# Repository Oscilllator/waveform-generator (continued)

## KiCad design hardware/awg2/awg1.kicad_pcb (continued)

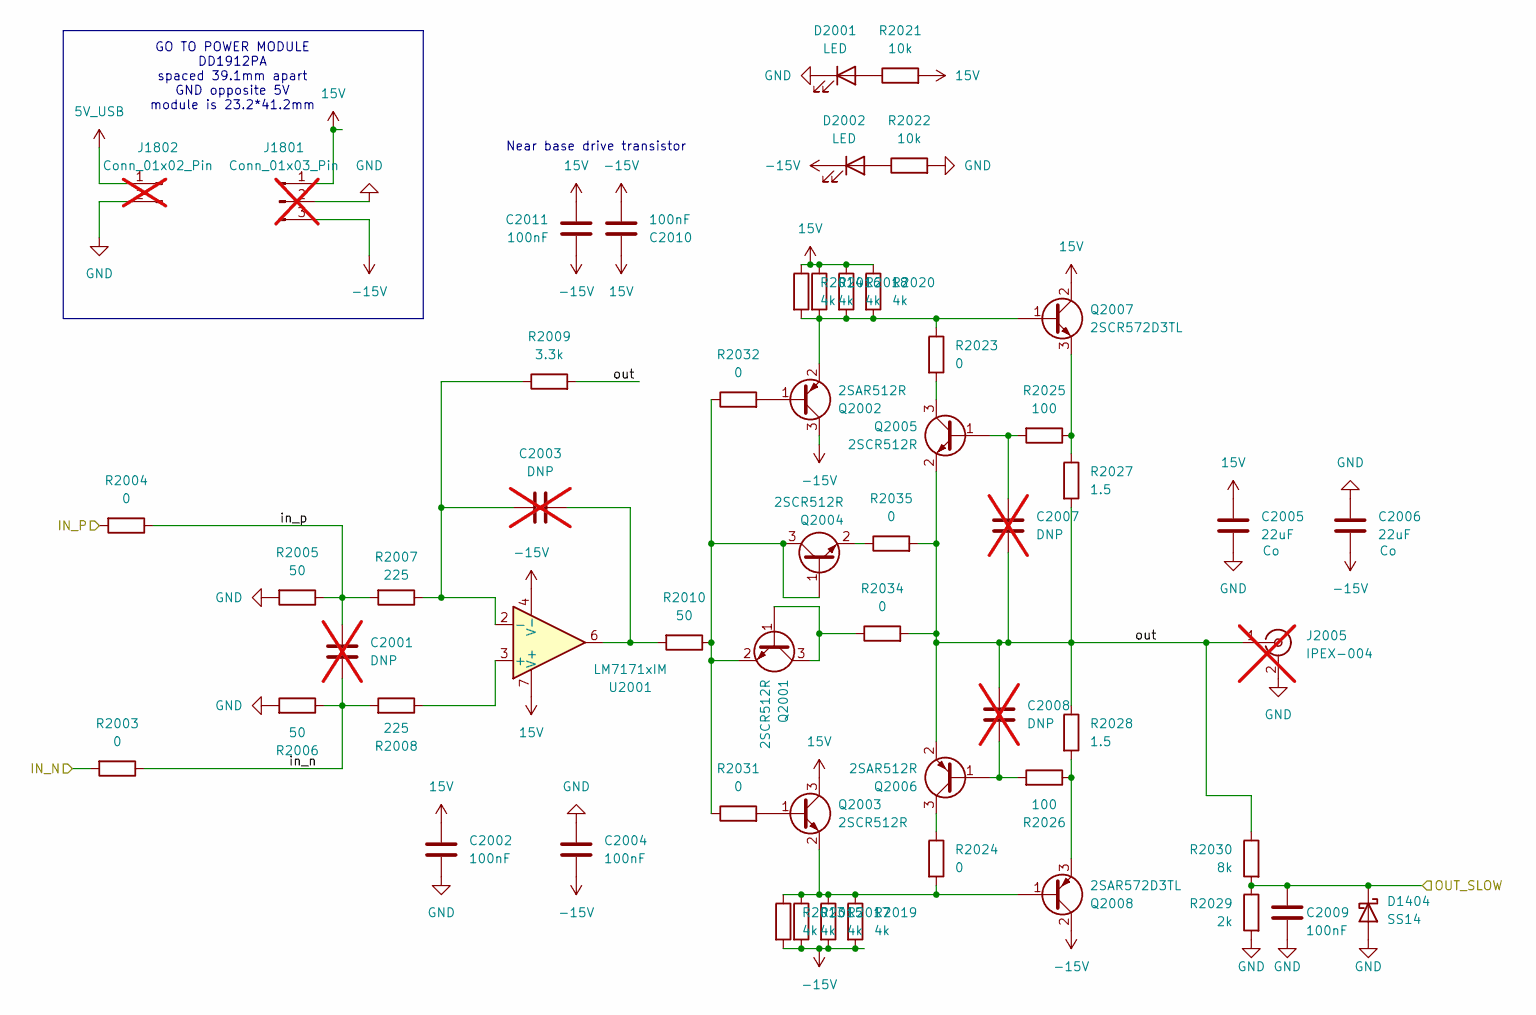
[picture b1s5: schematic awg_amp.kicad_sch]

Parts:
C2001: DNP; C_0603_1608Metric; LCSC C21120; not fitted
C2002, C2004, C2009, C2010, C2011: 100nF; C_0603_1608Metric; LCSC C1634
C2003, C2007, C2008: DNP; C_0603_1608Metric; LCSC C1634; not fitted
C2005, C2006: 22uF; C_1206_3216Metric
D1404: SS14; D_SMA
D2001, D2002: LED; D_0603_1608Metric; LCSC C2286
J1801: Conn_01x03_Pin; PinHeader_1x03_P2.54mm_Vertical; not fitted
J1802: Conn_01x02_Pin; PinHeader_1x02_P2.54mm_Vertical; not fitted
J2005: IPEX-004; SMA_Amphenol_132289_EdgeMount; not fitted
Q2001, Q2003, Q2004, Q2005: 2SCR512R; SOT-23
Q2002, Q2006: 2SAR512R; SOT-23
Q2007: 2SCR572D3TL; TO-252-2
Q2008: 2SAR572D3TL; TO-252-2
R2003, R2004, R2023, R2024, R2031, R2032, R2034, R2035: 0; R_0603_1608Metric; LCSC C21189
R2005, R2006, R2010: 50; R_0603_1608Metric; LCSC C23185
R2007, R2008: 225; R_0603_1608Metric; LCSC C22962
R2009: 3.3k; R_0603_1608Metric; LCSC C22975
R2013, R2014, R2015, R2016, R2017, R2018, R2019, R2020: 4k; R_0603_1608Metric; LCSC C23138
R2021, R2022: 10k; R_0603_1608Metric; LCSC C25804
R2025, R2026: 100; R_0603_1608Metric; LCSC C22775
R2027, R2028: 1.5; R_0603_1608Metric
R2029: 2k; R_0603_1608Metric
R2030: 8k; R_0603_1608Metric; LCSC C23138
U2001: LM7171xIM; SOIC-8_3.9x4.9mm_P1.27mm; LCSC C111821

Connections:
5V_USB: J1802.1; also elsewhere on the board
15V: C2002.1, C2005.1, C2010.1, C2011.1, J1801.1, Q2003.3 (C), Q2007.2 (C), R2014.1, R2016.1, R2018.1, R2020.1, R2021.2, U2001.7 (V+)
-15V: C2004.2, C2006.2, C2010.2, C2011.2, D2002.1 (K), J1801.3, Q2002.3 (C), Q2008.2 (C), R2013.2, R2015.2, R2017.2, R2019.2, U2001.4 (V-)
/AD9744/OUT_N: R2003.2; also elsewhere on the board
/AD9744/OUT_P: R2004.2; also elsewhere on the board
/awg_amp/OUT_SLOW: C2009.1, D1404.1 (K), R2029.1, R2030.2; also elsewhere on the board
/awg_amp/in_n: C2001.2, R2003.1, R2006.1, R2008.2
/awg_amp/in_p: C2001.1, R2004.1, R2005.1, R2007.2
/awg_amp/out: C2007.2, C2008.1, J2005.1 (In), Q2005.2 (E), Q2006.2 (E), R2009.2, R2027.2, R2028.1, R2030.1, R2034.2, R2035.2
GND: C2002.2, C2004.1, C2005.2, C2006.1, C2009.2, D1404.2 (A), D2001.1 (K), J1801.2, J1802.2, J2005.2 (Ext), R2005.2, R2006.2, R2022.2, R2029.2; also elsewhere on the board
unnamed: C2003.1, R2010.2, U2001.6
unnamed: D2001.2 (A), R2021.1
unnamed: D2002.2 (A), R2022.1
unnamed: Q2001.1 (B), Q2001.3 (C), R2034.1
unnamed: Q2001.2 (E), Q2004.1 (B), Q2004.3 (C), R2010.1, R2031.1, R2032.1
unnamed: Q2002.1 (B), R2032.2
unnamed: Q2002.2 (E), Q2007.1 (B), R2014.2, R2016.2, R2018.2, R2020.2, R2023.1
unnamed: Q2003.1 (B), R2031.2
unnamed: Q2003.2 (E), Q2008.1 (B), R2013.1, R2015.1, R2017.1, R2019.1, R2024.2
unnamed: Q2004.2 (E), R2035.1
unnamed: C2007.1, Q2005.1 (B), R2025.2
unnamed: Q2005.3 (C), R2023.2
unnamed: C2008.2, Q2006.1 (B), R2026.2
unnamed: Q2006.3 (C), R2024.1
unnamed: Q2007.3 (E), R2025.1, R2027.1
unnamed: Q2008.3 (E), R2026.1, R2028.2
unnamed: R2008.1, U2001.3 (+)
unnamed: C2003.2, R2007.1, R2009.1, U2001.2 (-)

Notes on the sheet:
GO TO POWER MODULE DD1912PA spaced 39.1mm apart GND opposite 5V module is 23.2*41.2mm
Near base drive transistor

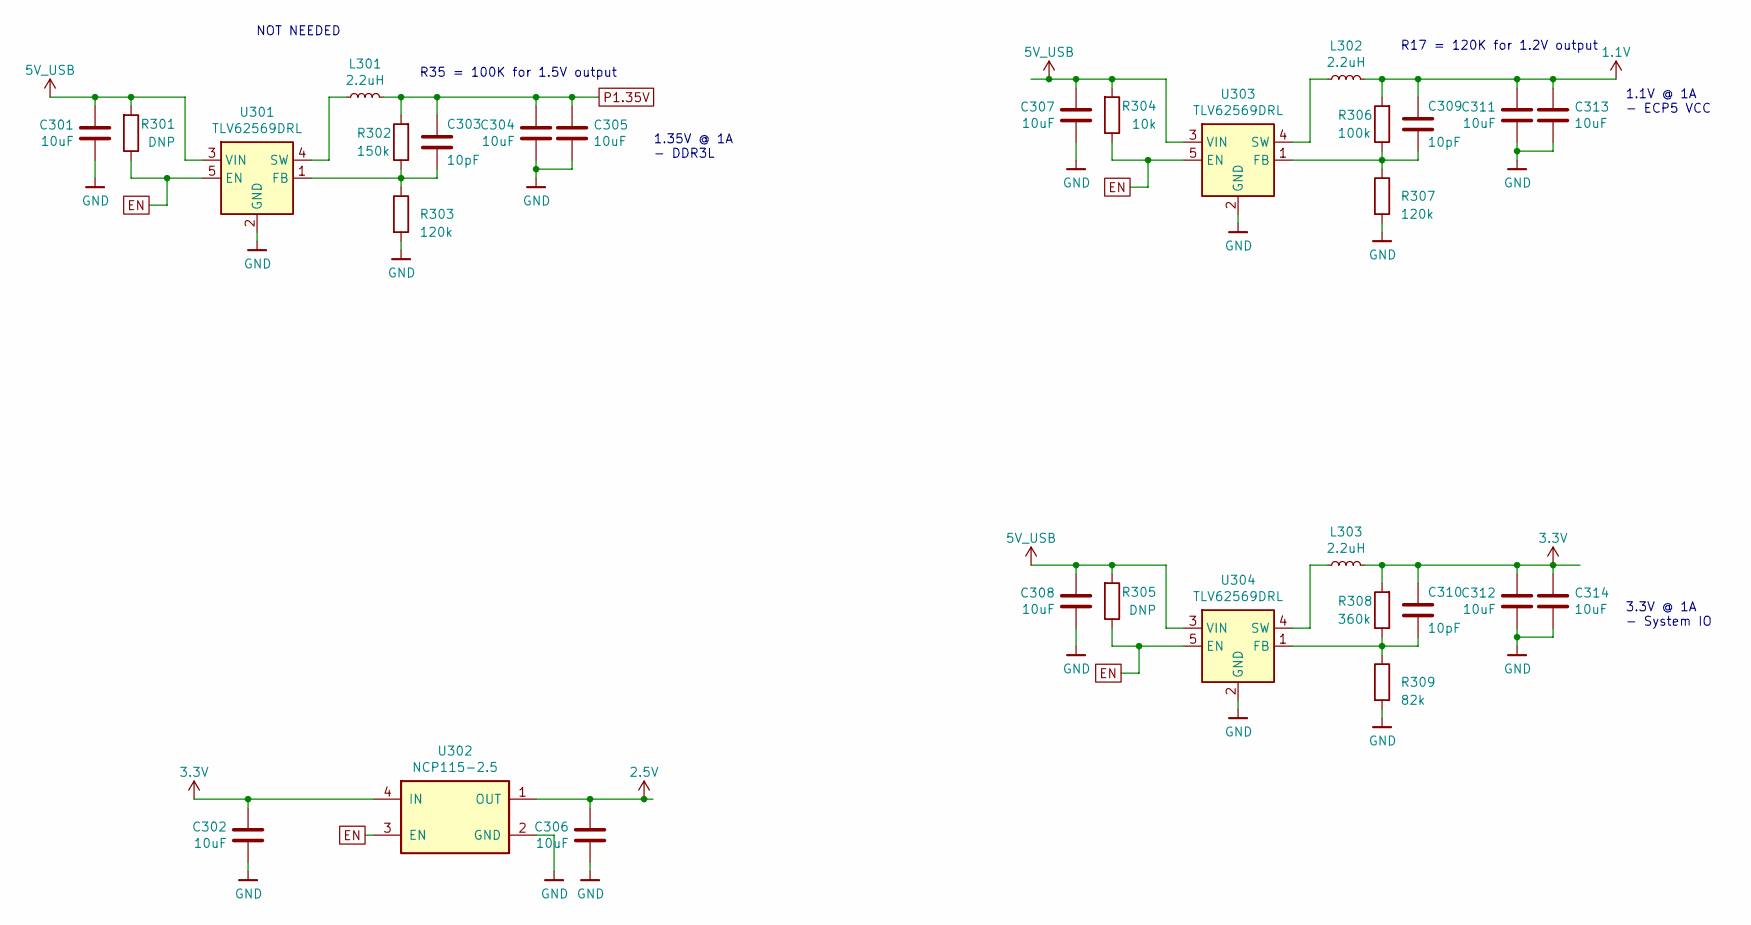
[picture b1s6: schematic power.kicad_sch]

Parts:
C301, C302, C304, C305, C306, C307, C308, C311, C312, C313, C314: 10uF; C_0603_1608Metric
C303, C309, C310: 10pF; C_0603_1608Metric
L301, L302, L303: 2.2uH; L_0805_2012Metric
R301, R305: DNP; C_0603_1608Metric
R302: 150k; C_0603_1608Metric
R303, R307: 120k; C_0603_1608Metric
R304: 10k; C_0603_1608Metric
R306: 100k; C_0603_1608Metric
R308: 360k; C_0603_1608Metric
R309: 82k; C_0603_1608Metric
U301, U303, U304: TLV62569DRL; SOT-563
U302: NCP115-2.5; Texas_X2SON-4_1x1mm_P0.65mm

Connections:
1.1V: C309.2, C311.2, C313.2, L302.2, R306.2; also elsewhere on the board
2.5V: C306.2, U302.1 (OUT); also elsewhere on the board
3.3V: C302.2, C310.2, C312.2, C314.2, L303.2, R308.2, U302.4 (IN); also elsewhere on the board
5V_USB: C301.2, C307.2, C308.2, R301.2, R304.2, R305.2, U301.3 (VIN), U303.3 (VIN), U304.3 (VIN); also elsewhere on the board
EN: R301.1, R304.1, R305.1, U301.5 (EN), U302.3 (EN), U303.5 (EN), U304.5 (EN)
GND: C301.1, C302.1, C304.1, C305.1, C306.1, C307.1, C308.1, C311.1, C312.1, C313.1, C314.1, R303.2, R307.2, R309.2, U301.2 (GND), U302.2 (GND), U303.2 (GND), U304.2 (GND); also elsewhere on the board
unnamed: C303.1, R302.1, R303.1, U301.1 (FB)
unnamed: C303.2, C304.2, C305.2, L301.2, R302.2
unnamed: L301.1, U301.4 (SW)
unnamed: C309.1, R306.1, R307.1, U303.1 (FB)
unnamed: L302.1, U303.4 (SW)
unnamed: C310.1, R308.1, R309.1, U304.1 (FB)
unnamed: L303.1, U304.4 (SW)

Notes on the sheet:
1.1V @ 1A - ECP5 VCC
1.35V @ 1A - DDR3L
3.3V @ 1A - System IO
R35 = 100K for 1.5V output
R17 = 120K for 1.2V output
NOT NEEDED

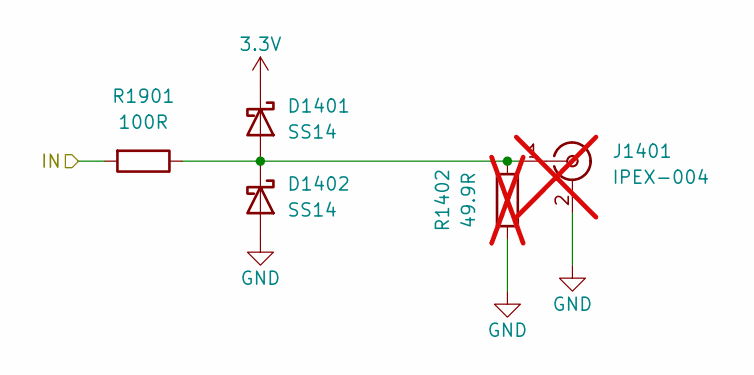
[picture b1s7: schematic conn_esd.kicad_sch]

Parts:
D1401, D1402: SS14; D_SMA
J1401: IPEX-004; SMA_Amphenol_132289_EdgeMount; not fitted
R1402: 49.9R; R_0603_1608Metric; not fitted
R1901: 100R; R_0603_1608Metric

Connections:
3.3V: D1401.1 (K); also elsewhere on the board
/fpga/DOUT1: R1901.2; also elsewhere on the board
GND: D1402.2 (A), J1401.2 (Ext), R1402.1; also elsewhere on the board
unnamed: D1401.2 (A), D1402.1 (K), J1401.1 (In), R1402.2, R1901.1

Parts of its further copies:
D1501, D1502, D1601, D1602, D1701, D1702: SS14; D_SMA
J1501, J1601, J1701: IPEX-004; SMA_Amphenol_132289_EdgeMount; not fitted
R1502, R1602, R1702: 49.9R; R_0603_1608Metric; not fitted
R1903, R1904, R1905: 100R; R_0603_1608Metric

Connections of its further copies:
3.3V: D1501.1 (K), D1601.1 (K), D1701.1 (K); also elsewhere on the board
/fpga/DOUT0: R1905.2; also elsewhere on the board
/fpga/REFCLK: R1904.2; also elsewhere on the board
/fpga/TRIG: R1903.2; also elsewhere on the board
GND: D1502.2 (A), D1602.2 (A), D1702.2 (A), J1501.2 (Ext), J1601.2 (Ext), J1701.2 (Ext), R1502.1, R1602.1, R1702.1; also elsewhere on the board
unnamed: D1501.2 (A), D1502.1 (K), J1501.1 (In), R1502.2, R1903.1
unnamed: D1601.2 (A), D1602.1 (K), J1601.1 (In), R1602.2, R1904.1
unnamed: D1701.2 (A), D1702.1 (K), J1701.1 (In), R1702.2, R1905.1

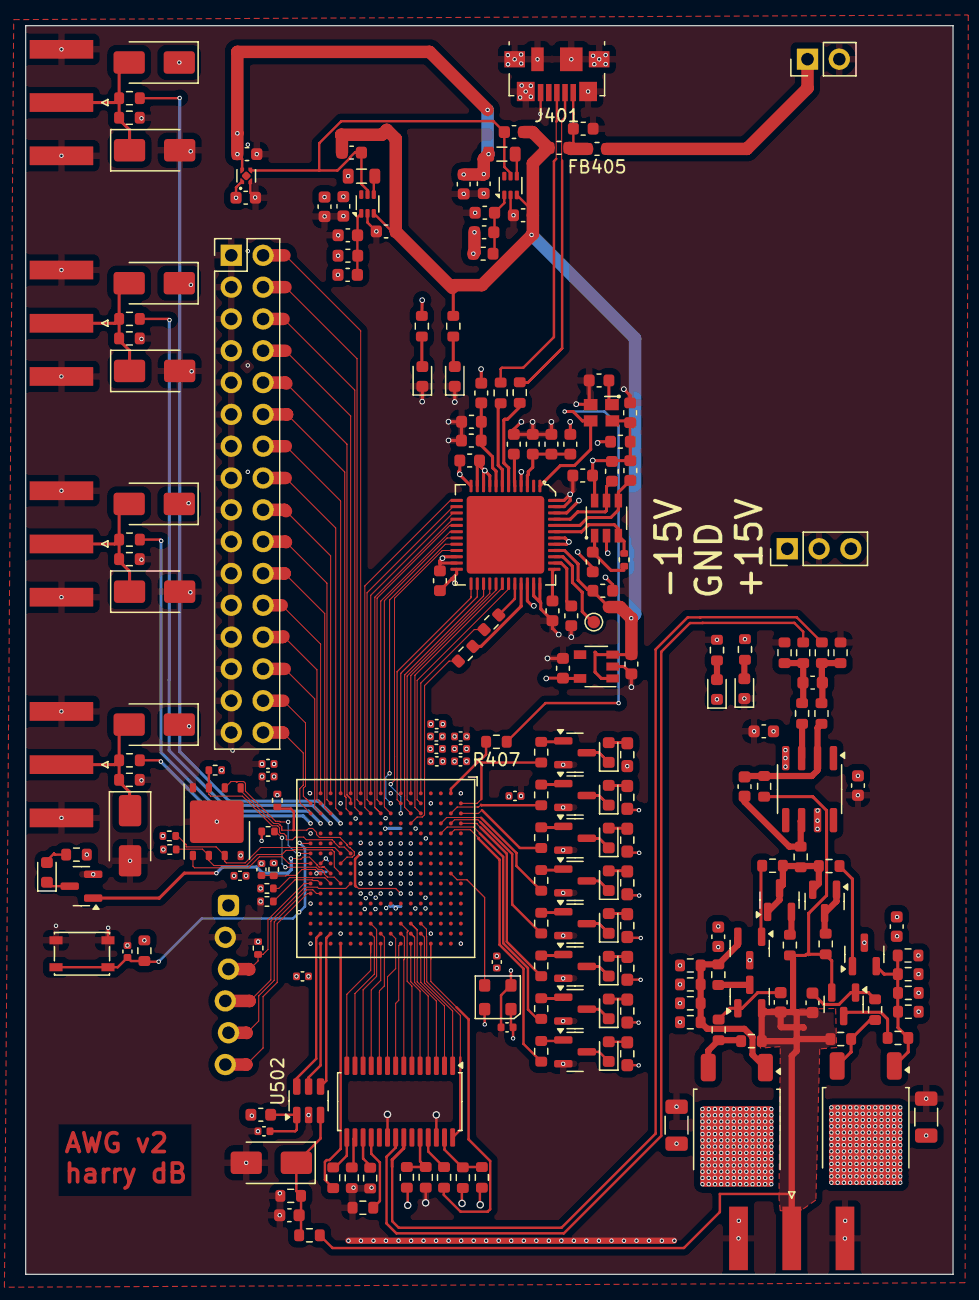
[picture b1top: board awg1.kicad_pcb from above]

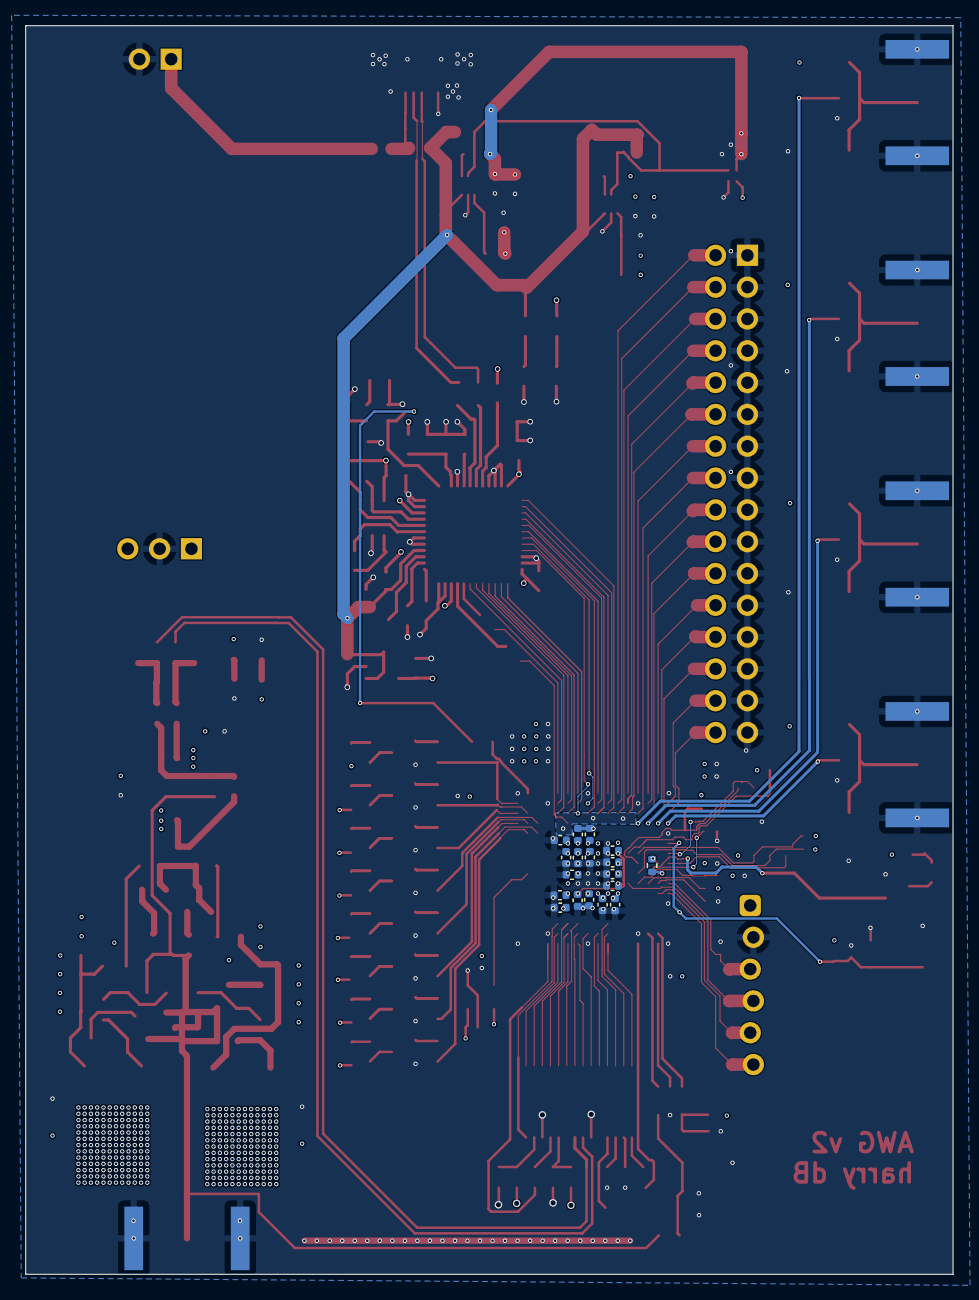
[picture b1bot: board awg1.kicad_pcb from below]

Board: 6 copper layers, 74.0 x 99.7 mm, 235 parts (18 on the bottom side), 180 nets.

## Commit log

2025-04-06 add readme
2025-04-06 update image
2025-04-06 add in the things
2025-05-17 fix ftdi C eeprom programming, and change vid and pid so that the linux triveer doesn't grab it
2025-05-17 add udev rules and eeprom programming instructions
2025-05-17 update instructions on how to use the product
2025-05-17 update docs
2025-05-17 clarify: awglib is the right choice
2025-05-17 fix misc bugs and make the package installable
2025-05-17 add json nonsense to gitignore
2025-05-17 add beginnings of rasterise example
2025-05-17 Add scrolling text example
